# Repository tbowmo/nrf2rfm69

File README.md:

# nrf2rfm69

Converter module to enable RFM69 ussage on NRF24 nodes in MySensors

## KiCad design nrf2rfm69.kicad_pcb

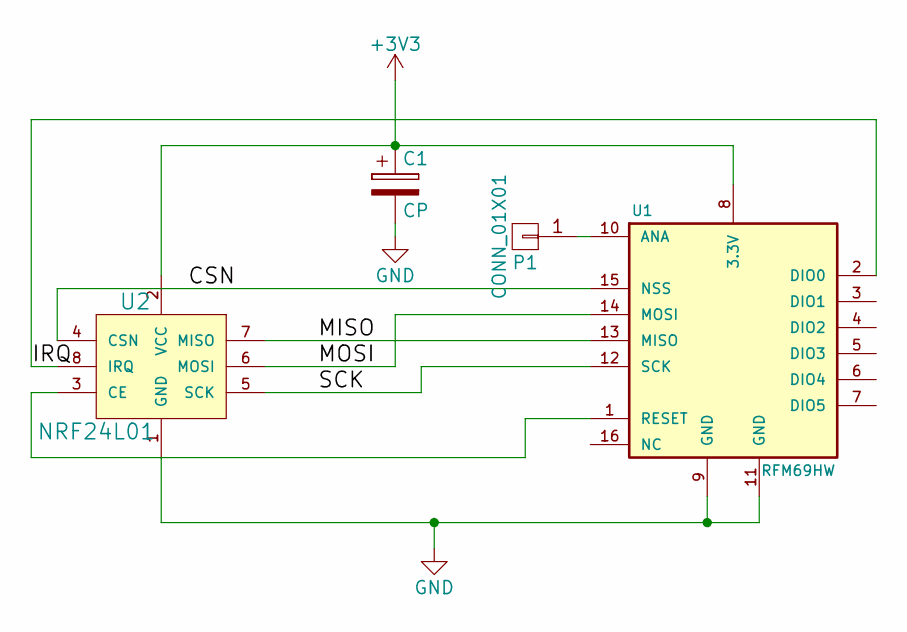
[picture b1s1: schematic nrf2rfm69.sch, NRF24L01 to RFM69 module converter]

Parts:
C1: CP; C_0805
P1: CONN_01X01; Socket_Strip_Angled_1x01
U1: RFM69HW; RFM69HW_SMD_Handsoldering
U2: NRF24L01; Socket_Strip_Straight_2x04

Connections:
+3V3: C1.1, U1.8 (3.3V), U2.2 (VCC)
/CSN: U1.15 (NSS), U2.4 (CSN)
/IRQ: U1.2 (DIO0), U2.8 (IRQ)
/MISO: U1.13 (MISO), U2.7 (MISO)
/MOSI: U1.14 (MOSI), U2.6 (MOSI)
/SCK: U1.12 (SCK), U2.5 (SCK)
GND: C1.2, U1.9 (GND), U1.11 (GND), U2.1 (GND)
unnamed: P1.1, U1.10 (ANA)
unnamed: U1.1 (RESET), U2.3 (CE)

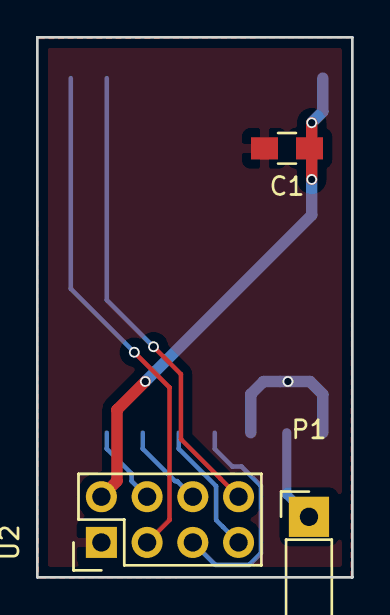
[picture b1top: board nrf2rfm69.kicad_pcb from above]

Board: 2 copper layers, 17.5 x 30.0 mm, 4 parts (1 on the bottom side), 9 nets.

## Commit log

2016-01-17 Added readme file
2016-01-17 Updated jpg of project
2016-01-27 Shrinked pcb a bit, and created panel layout for dirtypcb's
2016-02-03 Added CERN license files
2016-05-03 Added eagle formatted gerbers
